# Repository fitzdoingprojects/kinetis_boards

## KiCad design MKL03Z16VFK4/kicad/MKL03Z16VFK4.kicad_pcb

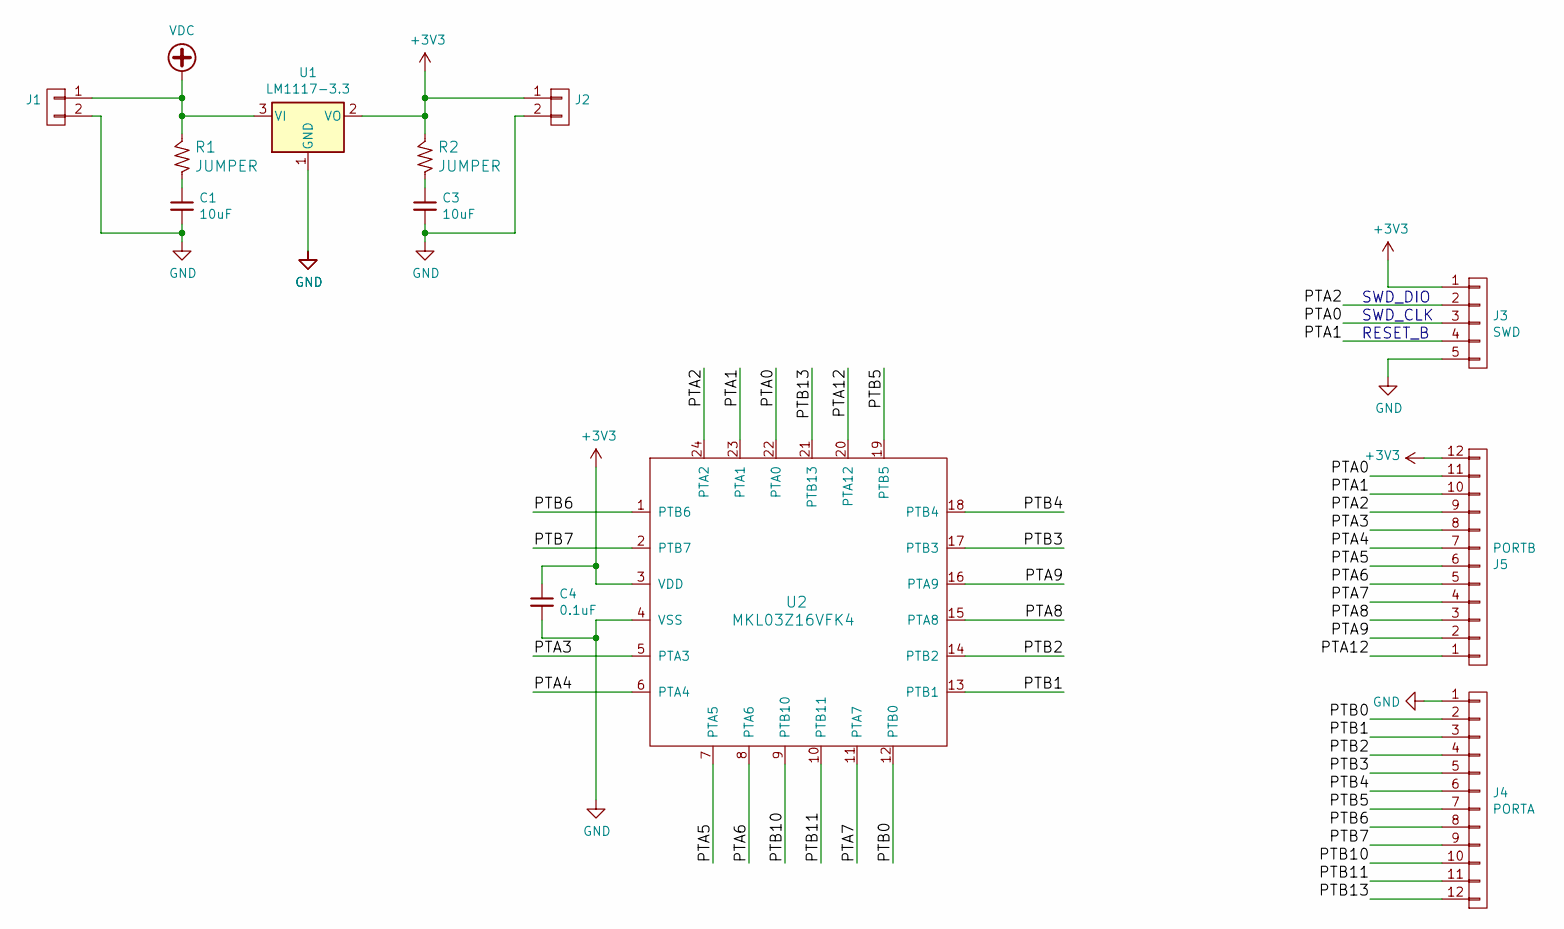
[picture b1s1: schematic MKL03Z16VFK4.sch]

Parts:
C1, C3: 10uF; C_0805
C4: 0.1uF; C_0402
J1, J2: CONN_01X02; Pin_Header_Straight_1x02_Pitch2.54mm
J3: SWD; Pin_Header_Straight_1x05_Pitch2.54mm
J4: PORTA; Pin_Header_Straight_1x12_Pitch2.54mm
J5: PORTB; Pin_Header_Straight_1x12_Pitch2.54mm
R1, R2: JUMPER; R_0402
U1: LM1117-3.3; SOT-223-3Lead_TabPin2
U2: MKL03Z16VFK4; QFN-24_EP_4x4_Pitch0.65mm

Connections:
+3V3: C4.1, J2.1, J3.1, J5.12, R2.2, U1.2 (VO), U2.3 (VDD)
/PTA0: J3.3, J5.11, U2.22 (PTA0)
/PTA1: J3.4, J5.10, U2.23 (PTA1)
/PTA2: J3.2, J5.9, U2.24 (PTA2)
/PTA3: J5.8, U2.5 (PTA3)
/PTA4: J5.7, U2.6 (PTA4)
/PTA5: J5.6, U2.7 (PTA5)
/PTA6: J5.5, U2.8 (PTA6)
/PTA7: J5.4, U2.11 (PTA7)
/PTA8: J5.3, U2.15 (PTA8)
/PTA9: J5.2, U2.16 (PTA9)
/PTA12: J5.1, U2.20 (PTA12)
/PTB0: J4.2, U2.12 (PTB0)
/PTB1: J4.3, U2.13 (PTB1)
/PTB2: J4.4, U2.14 (PTB2)
/PTB3: J4.5, U2.17 (PTB3)
/PTB4: J4.6, U2.18 (PTB4)
/PTB5: J4.7, U2.19 (PTB5)
/PTB6: J4.8, U2.1 (PTB6)
/PTB7: J4.9, U2.2 (PTB7)
/PTB10: J4.10, U2.9 (PTB10)
/PTB11: J4.11, U2.10 (PTB11)
/PTB13: J4.12, U2.21 (PTB13)
GND: C1.2, C3.2, C4.2, J1.2, J2.2, J3.5, J4.1, U1.1 (GND), U2.4 (VSS)
unnamed: C1.1, R1.1
unnamed: C3.1, R2.1
VDC: J1.1, R1.2, U1.3 (VI)

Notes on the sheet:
SWD_CLK
SWD_DIO
RESET_B

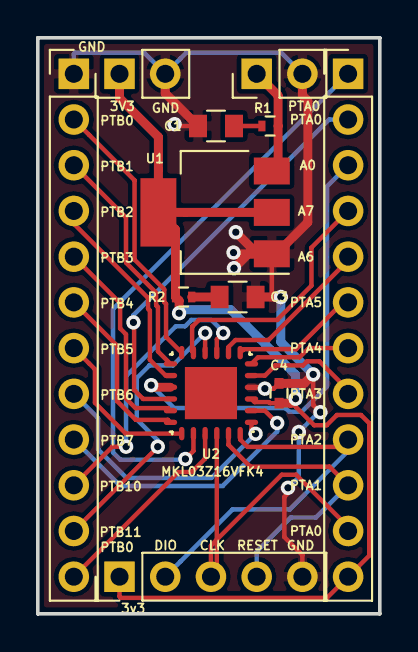
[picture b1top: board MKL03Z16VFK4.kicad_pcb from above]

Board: 2 copper layers, 19.0 x 32.0 mm, 12 parts (0 on the bottom side), 27 nets.

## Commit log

2017-10-18 first layout of board
